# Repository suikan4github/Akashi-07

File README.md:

# Akashi-07
SDR front end prototype for NUCLEO G431RB and F722ZE

## Functionality
This board is designed for testing the SDR with Quadrature Sampling Detector. 
The connectors can be directly mounted on the Arduino mono Rev3.

The design can be retrieved from the [github](https://github.com/suikan4github/Akashi-07) repository.

The schematics [can be downloaded](docs/Akashi-07.pdf) as PDF format. 

| Function | NUCLEO-G431RB | NUCLEO-F722ZE |
|----------|---------------|---------------|
| I2C1 SCL | PB8           | PB8           |
| I2C1 SDA | PB9           | PB9           |
| RESCUE   | PC9           | PC9           |

The configuration of special ports are :

- PC9 : Open Drain output. To save the struggled I2C device.

## I2C address
The I2C device address of Si5351 PLL is configured as ***0x60*** ( 7bit address ).

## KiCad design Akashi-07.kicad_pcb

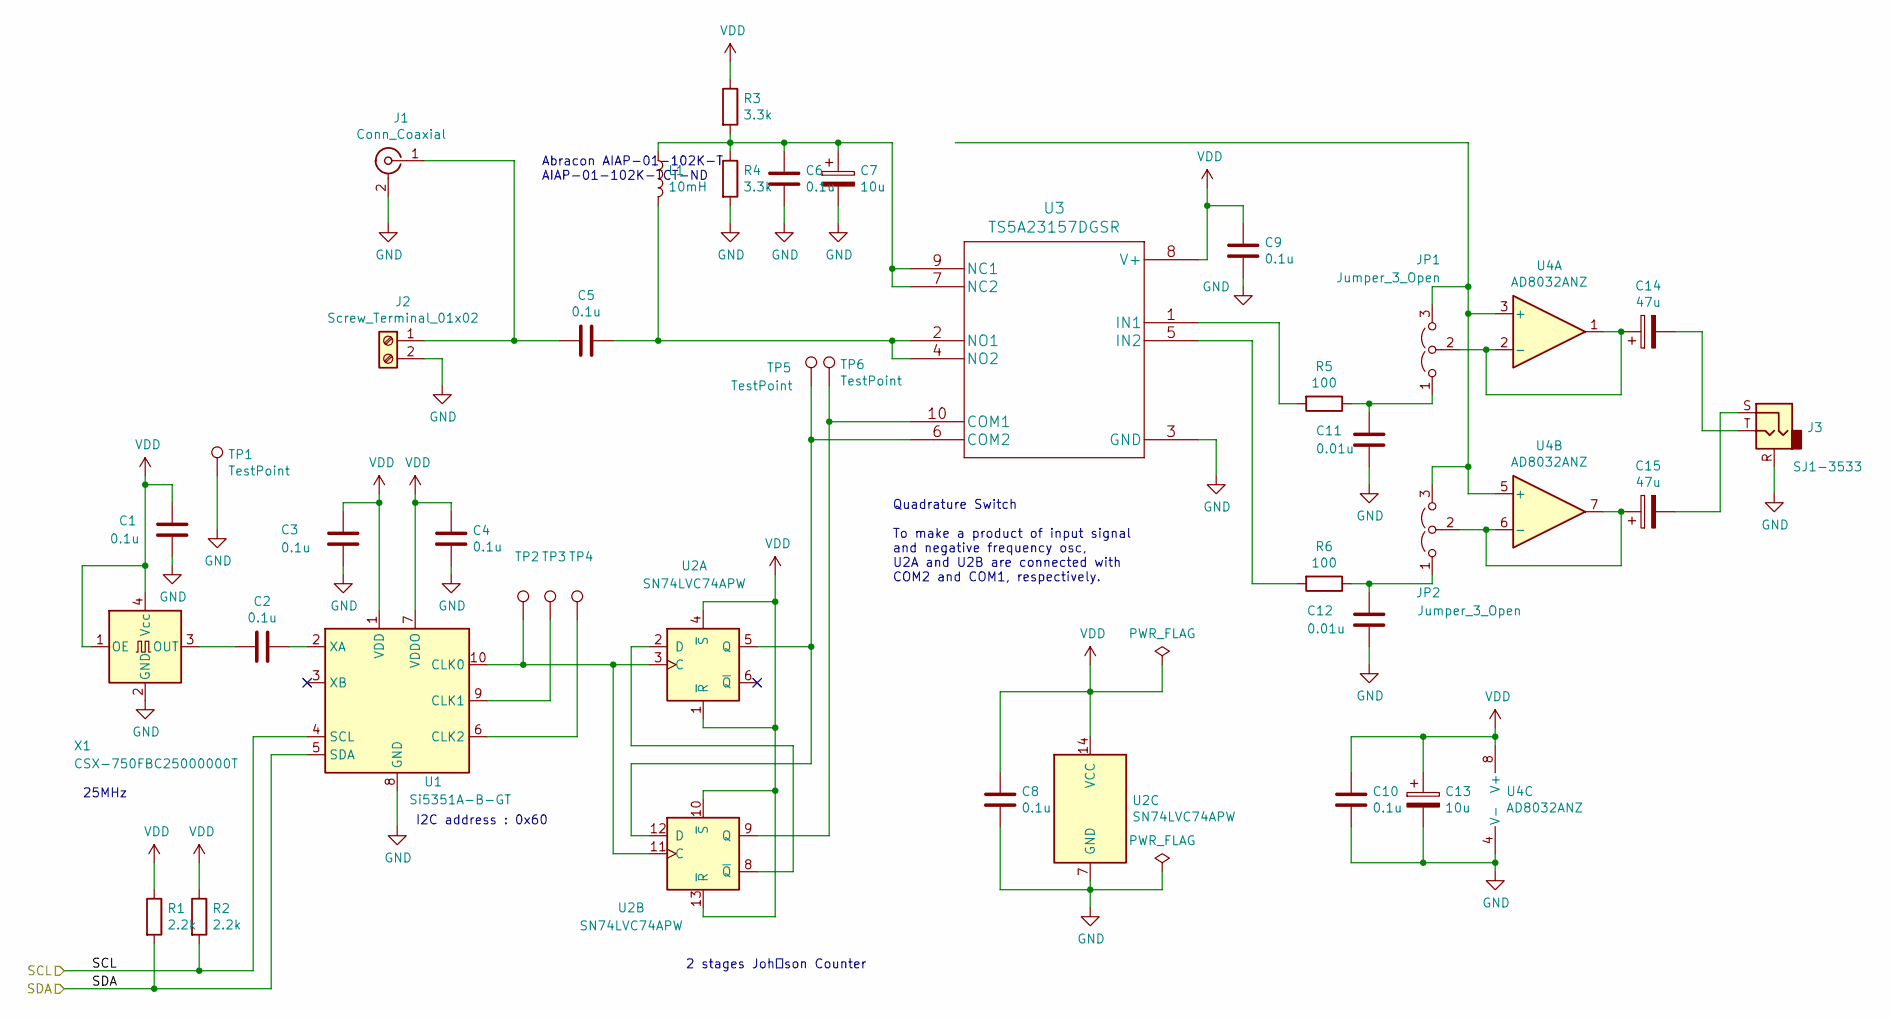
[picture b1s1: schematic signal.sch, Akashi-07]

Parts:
C1, C2, C3, C4, C5, C6, C8, C9, C10: 0.1u; C_Disc_D4.7mm_W2.5mm_P5.00mm
C7, C13: 10u; CP_Radial_D8.0mm_P2.50mm
C11, C12: 0.01u; C_Disc_D4.7mm_W2.5mm_P5.00mm
C14, C15: 47u; CP_Radial_D8.0mm_P2.50mm
J1: Conn_Coaxial; SMA_THT_Jack_Straight; DigiKey WM5543-ND
J2: Screw_Terminal_01x02; TerminalBlock_bornier-2_P5.08mm; DigiKey 281-2888-ND
J3: SJ1-3533; Jack_3.5mm_CUI_SJ1-3533NG_Horizontal_CircularHoles; DigiKey CP1-3533N-ND
JP1, JP2: Jumper_3_Open; Pin_Header_Straight_1x03_Pitch2.54mm
L1: 10mH; L_Axial_L7.0mm_D3.3mm_P5.08mm_Vertical_Fastron_MICC; DigiKey AIAP-01-102K-TCT-ND
R1, R2: 2.2k; R_Axial_DIN0204_L3.6mm_D1.6mm_P2.54mm_Vertical
R3, R4: 3.3k; R_Axial_DIN0204_L3.6mm_D1.6mm_P2.54mm_Vertical
R5, R6: 100; R_Axial_DIN0204_L3.6mm_D1.6mm_P2.54mm_Vertical
TP1, TP2, TP3, TP4, TP5, TP6: TestPoint; Measurement_Point_Round-TH_Big
U1: Si5351A-B-GT; MSOP-10_3x3mm_Pitch0.5mm; DigiKey 336-2399-5-ND
U2: SN74LVC74APW; TSSOP-14_4.4x5mm_Pitch0.65mm; DigiKey 296-1241-1-ND
U3: TS5A23157DGSR; DigiKey 296-17076-1-ND
U4: AD8032ANZ; DIP-8_W7.62mm; DigiKey AD8032ANZ-ND
X1: CSX-750FBC25000000T; Oscillator_SMD_SeikoEpson_SG8002CA-4pin_7.0x5.0mm_HandSolde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; DigiKey 300-7246-1-ND

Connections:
/connector/SCL: R2.2, U1.4 (SCL); also elsewhere on the board
/connector/SDA: R1.2, U1.5 (SDA); also elsewhere on the board
GND: C1.2, C3.2, C4.2, C6.2, C7.2, C8.2, C9.2, C10.2, C11.2, C12.2, C13.2, J1.2 (Ext), J2.2, J3.R, R4.2, TP1.1, U1.8 (GND), U2.7 (GND), U3.3 (GND), U4.4 (V-), X1.2 (GND); also elsewhere on the board
unnamed: C2.1, U1.2 (XA)
unnamed: C2.2, X1.3 (OUT)
unnamed: C5.1, L1.2, U3.2 (NO1), U3.4 (NO2)
unnamed: C5.2, J1.1 (In), J2.1
unnamed: C6.1, C7.1, L1.1, R3.2, R4.1, U3.7 (NC2), U3.9 (NC1)
unnamed: C11.1, JP1.1 (A), R5.1
unnamed: C12.1, JP2.1 (A), R6.1
unnamed: C14.1, JP1.2 (C), U4.1, U4.2 (-)
unnamed: C14.2, J3.T
unnamed: C15.1, JP2.2 (C), U4.6 (-), U4.7
unnamed: C15.2, J3.S
unnamed: JP1.3 (B), JP2.3 (B), U4.3 (+), U4.5 (+)
unnamed: R5.2, U3.1 (IN1)
unnamed: R6.2, U3.5 (IN2)
unnamed: TP2.1, U1.10 (CLK0), U2.3 (C), U2.11 (C)
unnamed: TP3.1, U1.9 (CLK1)
unnamed: TP4.1, U1.6 (CLK2)
unnamed: TP5.1, U2.5 (Q), U2.12 (D), U3.6 (COM2)
unnamed: TP6.1, U2.9 (Q), U3.10 (COM1)
unnamed: U2.2 (D), U2.8 (~Q)
VDD: C1.1, C3.1, C4.1, C8.1, C9.1, C10.1, C13.1, R1.1, R2.1, R3.1, U1.1 (VDD), U1.7 (VDDO), U2.1 (~R), U2.4 (~S), U2.10 (~S), U2.13 (~R), U2.14 (VCC), U3.8 (V+), U4.8 (V+), X1.1 (OE), X1.4 (Vcc); also elsewhere on the board

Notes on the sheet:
2 stages Johｎson Counter
Quadrature Switch To make a product of input signal and negative frequency osc, U2A and U2B are connected with COM2 and COM1, respectively.
I2C address : 0x60
25MHz
Abracon AIAP-01-102K-T AIAP-01-102K-TCT-ND

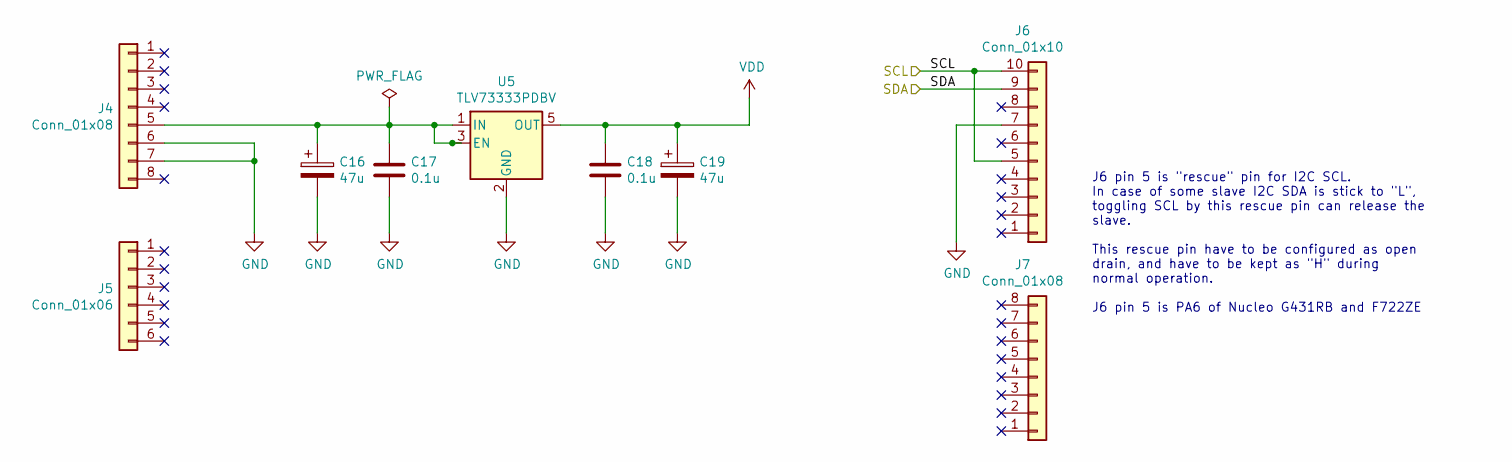
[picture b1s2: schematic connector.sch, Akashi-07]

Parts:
C16, C19: 47u; CP_Radial_D8.0mm_P2.50mm
C17, C18: 0.1u; C_Disc_D4.7mm_W2.5mm_P5.00mm
J4, J7: Conn_01x08; Pin_Header_Straight_1x08_Pitch2.54mm
J5: Conn_01x06; Pin_Header_Straight_1x06_Pitch2.54mm
J6: Conn_01x10; Pin_Header_Straight_1x10_Pitch2.54mm
U5: TLV73333PDBV; SOT-23-5_HandSoldering

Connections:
/connector/SCL: J6.5, J6.10; also elsewhere on the board
/connector/SDA: J6.9; also elsewhere on the board
GND: C16.2, C17.2, C18.2, C19.2, J4.6, J4.7, J6.7, U5.2 (GND); also elsewhere on the board
unnamed: C16.1, C17.1, J4.5, U5.1 (IN), U5.3 (EN)
VDD: C18.1, C19.1, U5.5 (OUT); also elsewhere on the board

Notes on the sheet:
J6 pin 5 is "rescue" pin for I2C SCL. In case of some slave I2C SDA is stick to "L", toggling SCL by this rescue pin can release the slave. This rescue pin have to be configured as open drain, and have to be kept as "H" during normal operation. J6 pin 5 is PA6 of Nucleo G431RB and F722ZE

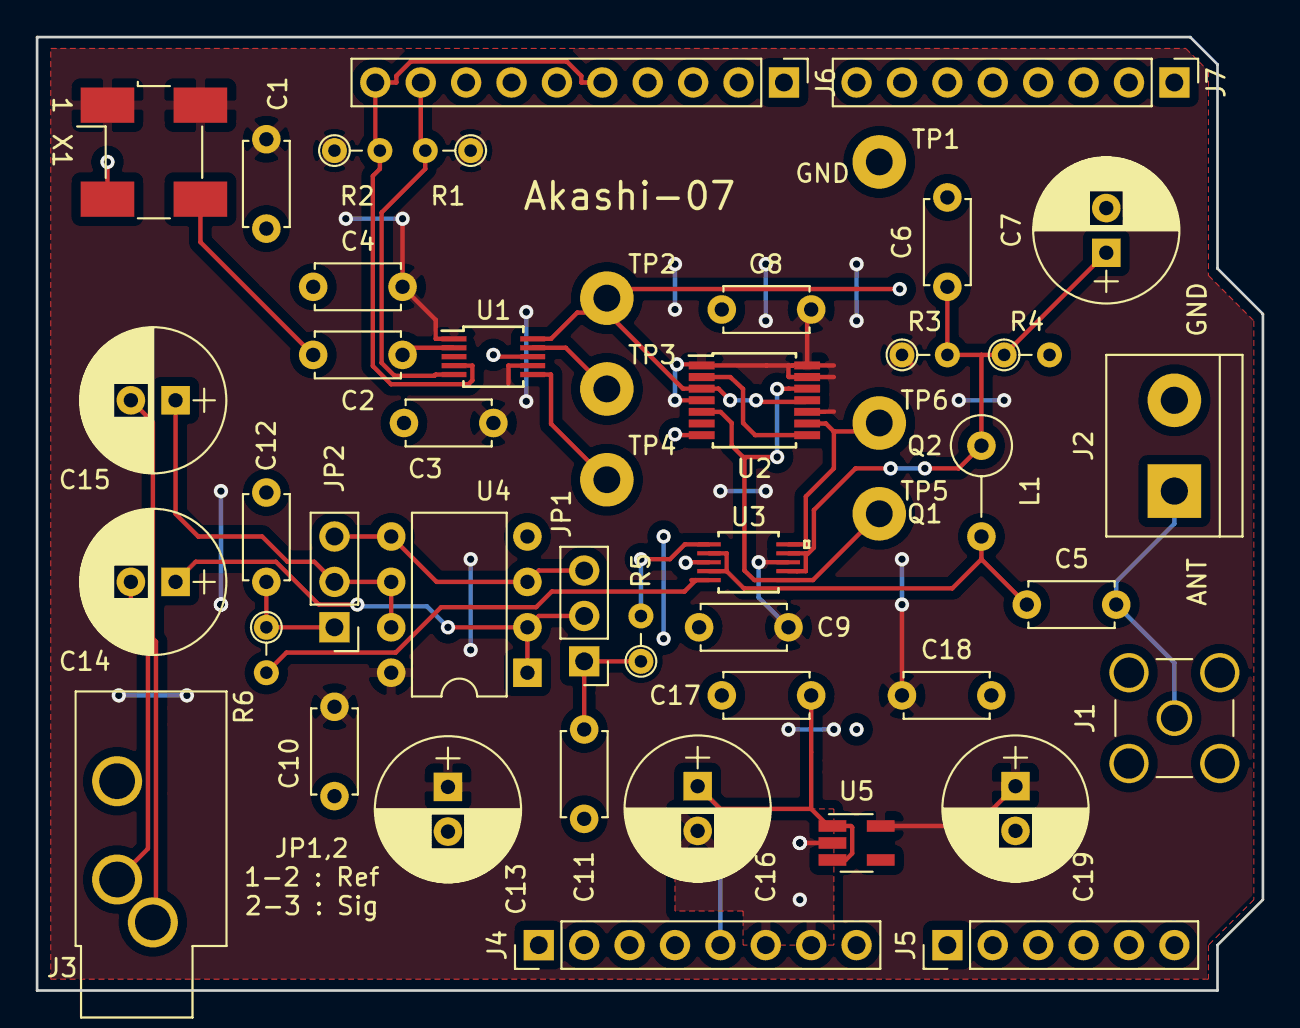
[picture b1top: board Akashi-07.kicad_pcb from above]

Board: 2 copper layers, 68.6 x 53.3 mm, 47 parts (0 on the bottom side), 25 nets.

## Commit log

2020-07-10 Added new devices.
    - OpAmps
    - 7474
2020-07-10 Update the switch symbol
    Singal flow is natural now.
2020-07-11 Analog part is haf complete
    Need to fix the value.
    Need to re-annotate
2020-07-11 Editing the schematics.
    Added bypass capacitor values.
    Added foot prints.
2020-07-11 Schematics are almost done.
    Audio jack is not yet.
2020-07-11 Footprint done.
    Added footprint of the audio jack.
    The documentation link of the each IC is done.
2020-07-12 All parts is on the PCB.
2020-07-12 Refined symbol names
    Adjust the position.
    Added copyright and board name.
2020-07-12 Routing finished.
2020-07-12 Added jumper to short the op-amp.
2020-07-13 Change TA48L033F foot print
    Added VDD plane on the FC layer.
2020-07-18 BOM is ready
2020-07-19 update BOM
2020-07-20 Ready for FusionPCB and Digikey

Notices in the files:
Akashi-07.kicad_pcb:
Akashi-07 : (C) 2020 Seiichi Horie
parts and their libraries:
Copyright 2016 Accelerated Designs. All rights reserved.
